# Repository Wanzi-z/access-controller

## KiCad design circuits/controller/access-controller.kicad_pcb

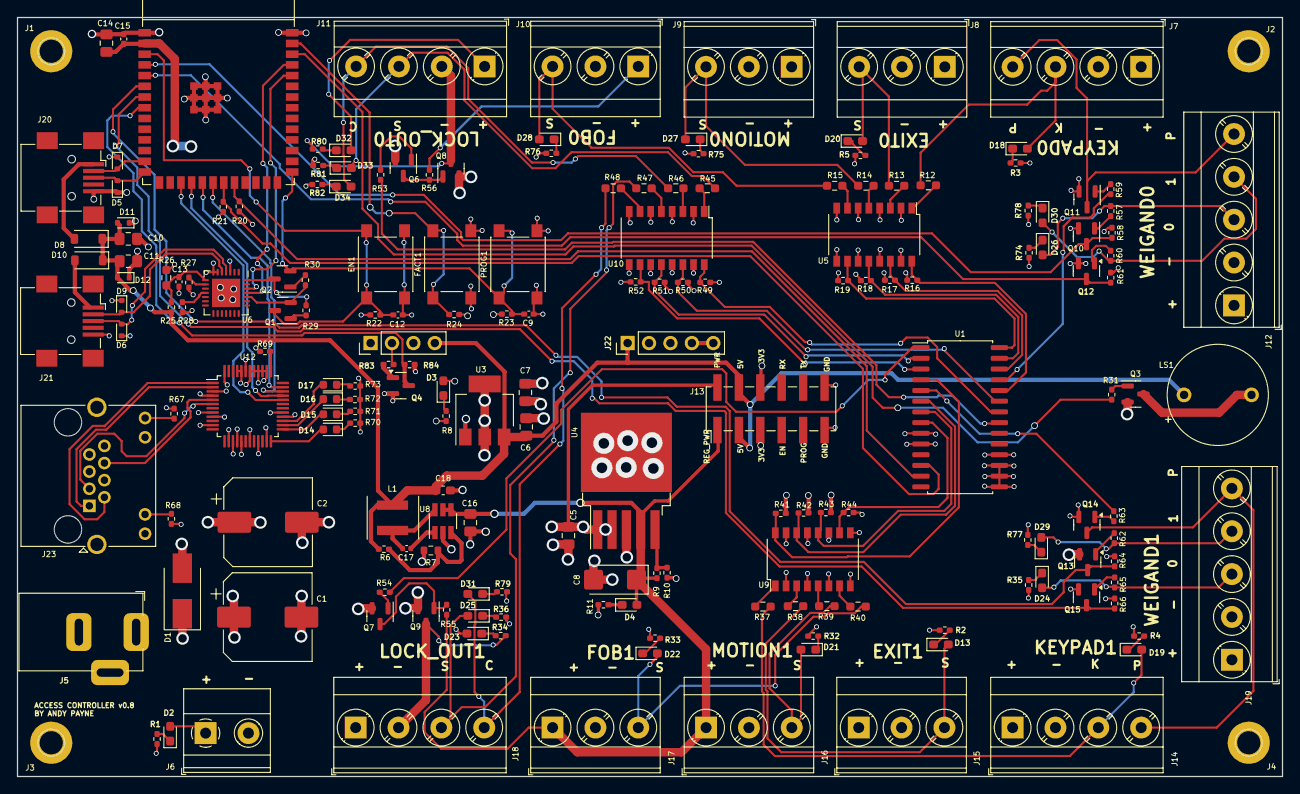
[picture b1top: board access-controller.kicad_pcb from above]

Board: 4 copper layers, 150.0 x 90.0 mm, 186 parts (0 on the bottom side), 138 nets.

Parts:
C1, C2: C_470uF; CP_Elec_10x10
C5, C6, C7, C10, C11, C14, C16: C_10uF; C_0805_2012Metric_Pad1.18x1.45mm_HandSolder
C8: C_10uF_Ta; CP_EIA-6032-15_Kemet-U_Pad2.25x2.35mm_HandSolder
C9, C12, C13: 1uF; C_0402_1005Metric_Pad0.74x0.62mm_HandSolder
C15: 100nF; C_0402_1005Metric_Pad0.74x0.62mm_HandSolder
C17: 22nF; C_0402_1005Metric
C18: C_22uF; C_0603_1608Metric_Pad1.08x0.95mm_HandSolder
D1: D_Zener; D_SMB_Handsoldering
D2, D3, D4, D13, D18, D19, D20, D21, D22, D23, D24, D25, D26, D27, D28, D29, D30, D31, D32, D33, D34: White; LED_0603_1608Metric_Pad1.05x0.95mm_HandSolder
D5, D6, D7, D9, D11, D12: ESD_5V; D_SOD-523
D8, D10: D_1N5819HW; D_SOD-123
D14, D15, D16, D17: Red; LED_0603_1608Metric
EN1: SW_PUSH; SW_SPST_PTS645
FACT1: SW_PUSH; SW_SPST_PTS645
J1, J2, J3, J4: Conn_01x01_Female; Mount_Hole
J5: Barrel_Jack_Switch; BarrelJack_OD5.5_ID2.5
J6: Screw_Terminal_01x02; TerminalBlock_Phoenix_MKDS-1,5-2-5.08_1x02_P5.08mm_Horizont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
J7, J11, J14, J18: Terminal_01x04; TerminalBlock_Phoenix_MKDS-3-4-5.08_1x04_P5.08mm_Horizontal
J8, J9, J10, J15, J16, J17: Terminal_01x03; TerminalBlock_Phoenix_MKDS-3-3-5.08_1x03_P5.08mm_Horizontal
J12, J19: Screw_Terminal_01x05; TerminalBlock_Phoenix_MKDS-3-5-5.08_1x05_P5.08mm_Horizontal
J13: Conn_02x06_Odd_Even; PinHeader_2x06_P2.54mm_Vertical_SMD
J20, J21: USB_MINI_B; USB_Mini-B_Wuerth_65100516121_Horizontal
J22: RF_MODULE; RXB6_RF_MODULE
J23: CONN_RJ45; RJ45_Amphenol_RJHSE538X
L1: 10uH; L_4x4
LS1: TMB12A05; S_YXDZ
PROG1: SW_PUSH; SW_SPST_PTS645
Q1: Q_L8050QLT1G; SOT-23
Q2: Q_L8550HQLT1G; SOT-23
Q3, Q4, Q6, Q7, Q10, Q11, Q12, Q13, Q14, Q15: Q_MMBT5551; SOT-23
Q8, Q9: Q_AO3400A; SOT-23
R1, R2, R3, R4, R5, R8, R11, R20, R21, R22, R23, R24, R28, R29, R30, R32, R33, R34, R35, R36, R67, R68, R74, R75, R76, R77, R78, R79, R80, R81, R82, R83, R84: 10K; R_0402_1005Metric_Pad0.72x0.64mm_HandSolder
R6: 100K; R_0402_1005Metric_Pad0.72x0.64mm_HandSolder
R7: 13K; R_0603_1608Metric
R9: R_20K; R_0402_1005Metric_Pad0.72x0.64mm_HandSolder
R10: R_2.2K; R_0402_1005Metric_Pad0.72x0.64mm_HandSolder
R12, R13, R14, R15, R37, R38, R39, R40, R45, R46, R47, R48: R_1K; R_0603_1608Metric_Pad0.98x0.95mm_HandSolder
R16, R17, R18, R19, R41, R42, R43, R44, R49, R50, R51, R52, R53, R54, R55, R56: R_10K_0402; R_0402_1005Metric_Pad0.72x0.64mm_HandSolder
R25: 22.1K; R_0402_1005Metric_Pad0.72x0.64mm_HandSolder
R26: 47.5K; R_0603_1608Metric_Pad0.98x0.95mm_HandSolder
R27, R69, R70, R71, R72, R73: 1K; R_0402_1005Metric_Pad0.72x0.64mm_HandSolder
R31, R59, R63: R_100; R_0402_1005Metric_Pad0.72x0.64mm_HandSolder
R57, R58, R60, R61, R62, R64, R65, R66: R_1K_0402; R_0402_1005Metric_Pad0.72x0.64mm_HandSolder
U1: MCP23017_SS; SOIC-28W_7.5x17.9mm_P1.27mm
U3: REG_AMS1117-3.3; SOT-223-3_TabPin2
U4: MIC29302WU; TO-263-5_TabPin3
U5, U9, U10: TLP291-4; SOP-16_4.4x10.4mm_P1.27mm
U6: CP2102N-Axx-xQFN28; QFN-28-1EP_5x5mm_P0.5mm_EP3.35x3.35mm
U7: ESP32-S3-WROOM-1
U8: REG_MT2492; SOT-23-6_Handsoldering
U12: W5500; LQFP-48_7x7mm_P0.5mm

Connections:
/3V3: C7.1, C14.1, C15.1, D3.2 (A), J13.5, J13.6, R16.1, R17.1, R18.1, R19.1, R20.1, R21.2, R22.1, R23.1, R24.1, R27.1, R41.1, R42.1, R43.1, R44.1, R49.1, R50.1, R51.1, R52.1, R58.2, R61.2, R64.2, R66.2, R67.2, R69.2, R84.1, U1.9 (VDD), U1.18 (~RESET), U3.2 (Vout), U6.6 (VDD), U6.7 (VREGIN), U7.2 (3V3), U12.4 (AVDD), U12.8 (AVDD), U12.11 (AVDD), U12.15 (AVDD), U12.17 (AVDD), U12.21 (AVDD), U12.28 (VDD), U12.43 (PMODE2)
/5V: C6.1, C10.1, C11.1, C18.1, D8.1 (K), D10.1 (K), D11.2 (A2), D12.2 (A2), J13.3, J13.4, J22.4, J22.5, L1.2, LS1.1, R6.1, R25.2, U3.3 (Vin)
/ANTENNA: J22.8, J22.9
/BUZZER: R31.1, U7.38 (GPIO2/TOUCH2/ADC1_CH1)
/CS: U7.17 (GPIO9/TOUCH9/ADC1_CH8/FSPIHD/SUBSPIHD), U12.32 (~SCS)
/DATA: J22.2, R83.2
/DATA_IO: Q4.3 (C), R84.2, U7.8 (GPIO15/U0RTS/ADC2_CH4/XTAL_32K_P)
/EXIT0: D20.2 (A), J8.3, R13.2
/EXIT0_SENSE: R17.2, U1.26 (GPA5), U5.14
/EXIT1: D13.2 (A), J15.3, R38.2
/EXIT1_SENSE: R42.2, U1.6 (GPB5), U9.14
/Ethernet/RX_N: J23.6, U12.5 (RXN)
/Ethernet/RX_P: J23.3, U12.6 (RXP)
/Ethernet/TX_N: J23.2, U12.1 (TXN)
/Ethernet/TX_P: J23.1, U12.2 (TXP)
/FOB0: D28.2 (A), J10.3, R15.2
/FOB0_SENSE: R19.2, U1.28 (GPA7), U5.10
/FOB1: D22.2 (A), J17.3, R40.2
/FOB1_SENSE: R44.2, U1.8 (GPB7), U9.10
/KEYPAD0: D18.2 (A), J7.3, R12.2
/KEYPAD0_SENSE: R16.2, U1.24 (GPA3), U5.16
/KEYPAD1: D19.2 (A), J14.3, R37.2
/KEYPAD1_SENSE: R41.2, U1.4 (GPB3), U9.16
/LOCK0_CLOSE: D34.2 (A), J11.4, R46.2
/LOCK0_CLOSE_IO: R50.2, U1.23 (GPA2), U10.14
/LOCK0_CONTROL: R53.2, U1.21 (GPA0)
/LOCK0_OUT: J11.2, Q8.3 (D), R80.1
/LOCK0_SENSE: R49.2, U1.22 (GPA1), U10.16
/LOCK0_STATE: D33.2 (A), J11.3, R45.2
/LOCK1_CLOSE: D31.2 (A), J18.4, R48.2
/LOCK1_CLOSE_IO: R52.2, U1.3 (GPB2), U10.10
/LOCK1_CONTROL: R54.2, U1.1 (GPB0)
/LOCK1_OUT: J18.2, Q9.3 (D), R34.1
/LOCK1_SENSE: R51.2, U1.2 (GPB1), U10.12
/LOCK1_STATE: D25.2 (A), J18.3, R47.2
/MISO: U7.20 (GPIO12/TOUCH12/ADC2_CH1/FSPICLK/FSPIIO6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), U12.34 (MISO)
/MOSI: U7.19 (GPIO11/TOUCH11/ADC2_CH0/FSPID/FSPIIO5/S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), U12.35 (MOSI)
/MOTION0: D27.2 (A), J9.3, R14.2
/MOTION0_SENSE: R18.2, U1.27 (GPA6), U5.12
/MOTION1: D21.2 (A), J16.3, R39.2
/MOTION1_SENSE: R43.2, U1.7 (GPB6), U9.12
/Microcontroller/D+: D6.2 (A2), J21.3 (D+), U6.4 (D+)
/Microcontroller/D-: D9.2 (A2), J21.2 (D-), U6.5 (D-)
/Microcontroller/DTR: Q2.3 (C), R29.1, U6.28 (~DTR)
/Microcontroller/EN: C12.1, EN1.1, Q1.3 (C), R22.2, U7.3 (EN)
/Microcontroller/FACT: FACT1.1, R24.2, U7.39 (GPIO1/TOUCH1/ADC1_CH0)
/Microcontroller/IO19: D7.2 (A2), J20.2 (D-), U7.13 (GPIO19/U1RTS/ADC2_CH8/CLK_OUT2/USB_D-)
/Microcontroller/IO20: D5.2 (A2), J20.3 (D+), U7.14 (GPIO20/U1CTS/ADC2_CH9/CLK_OUT1/USB_D+)
/Microcontroller/IO43: U6.25 (RXD), U7.37 (U0TXD/GPIO43/CLK_OUT1)
/Microcontroller/IO44: U6.26 (TXD), U7.36 (U0RXD/GPIO44/CLK_OUT2)
/Microcontroller/PROG: C9.1, PROG1.1, Q2.2 (E), R23.2, U7.27 (GPIO0/BOOT)
/Microcontroller/RTS: Q1.2 (E), R30.1, U6.24 (~RTS)
/POWER: C1.1, C2.1, C5.1, D1.1 (K), D2.2 (A), D23.2 (A), D32.2 (A), J5.1, J6.1, J11.1, J13.2, J18.1, J23.4, J23.5, R68.2, U4.1 (EN), U4.2 (IN)
/PUSH0: J7.4, J12.5, Q11.3 (C)
/PUSH0_IO: R59.1, U1.25 (GPA4)
/PUSH1: J14.4, J19.5, Q14.3 (C)
/PUSH1_IO: R63.1, U1.5 (GPB4)
/REG_POWER: C8.1, C16.1, D4.2 (A), J7.1, J8.1, J9.1, J10.1, J12.1, J13.1, J14.1, J15.1, J16.1, J17.1, J19.1, R9.1, R55.2, R56.2, U4.4 (Output), U8.4 (EN), U8.5 (VIN)
/SCL: R21.1, U1.12 (SCK), U7.21 (GPIO13/TOUCH13/ADC2_CH2/FSPIQ/FSPIIO7/S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)
/SCLK: U7.18 (GPIO10/TOUCH10/ADC1_CH9/FSPICS0/FSPIIO4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), U12.33 (SCLK)
/SDA: R20.2, U1.13 (SDA), U7.22 (GPIO14/TOUCH14/ADC2_CH3/FSPIWP/FSPIDQS/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)
/WG0_DATA0: D26.2 (A), J12.3, R57.2
/WG0_DATA1: D30.2 (A), J12.4, R60.2
/WG0_DATA_SENSE0: Q10.3 (C), R58.1, U7.4 (GPIO4/TOUCH4/ADC1_CH3)
/WG0_DATA_SENSE1: Q12.3 (C), R61.1, U7.5 (GPIO5/TOUCH5/ADC1_CH4)
/WG1_DATA0: D24.2 (A), J19.3, R65.2
/WG1_DATA1: D29.2 (A), J19.4, R62.2
/WG1_DATA_SENSE0: Q13.3 (C), R64.1, U7.6 (GPIO6/TOUCH6/ADC1_CH5)
/WG1_DATA_SENSE1: Q15.3 (C), R66.1, U7.7 (GPIO7/TOUCH7/ADC1_CH6)
GND: C1.2, C2.2, C5.2, C6.2, C7.2, C8.2, C9.2, C10.2, C11.2, C12.2, C13.2, C14.2, C15.2, C16.2, C18.2, D1.2 (A), D5.1 (A1), D6.1 (A1), D7.1 (A1), D9.1 (A1), D11.1 (A1), D12.1 (A1), EN1.2, FACT1.2, J1.1, J2.1, J3.1, J4.1, J5.2, J5.3, J6.2, J7.2, J8.2, J9.2, J10.2, J12.2, J13.11, J13.12, J14.2, J15.2, J16.2, J17.2, J19.2, J20.5 (GND), J21.5 (GND), J22.1, J22.6, J22.7, J23.7, J23.8, J23.9, J23.11, PROG1.2, Q3.2 (E), Q4.2 (E), Q6.2 (E), Q7.2 (E), Q8.2 (S), Q9.2 (S), Q10.2 (E), Q11.2 (E), Q12.2 (E), Q13.2 (E), Q14.2 (E), Q15.2 (E), R1.1, R2.1, R3.1, R4.1, R5.1, R7.2, R8.1, R10.2, R11.1, R26.1, R28.2, R32.1, R33.1, R35.1, R36.1, R70.2, R71.2, R72.2, R73.2, R74.1, R75.1, R76.1, R77.1, R78.1, R79.1, R81.1, R82.1, U1.10 (VSS), U1.15 (A0), U1.16 (A1), U1.17 (A2), U3.1 (GND), U4.3 (GND), U5.2, U5.4, U5.6, U5.8, U5.9, U5.11, U5.13, U5.15, U6.3 (GND), U6.29 (GND), U7.1 (GND), U7.40 (GND), U7.41 (GND), U8.2 (GND), U9.2, U9.4, U9.6, U9.8, U9.9, U9.11, U9.13, U9.15, U10.2, U10.4, U10.6, U10.8, U10.9, U10.11, U10.13, U10.15, U12.3 (AGND), U12.9 (AGND), U12.14 (AGND), U12.16 (AGND), U12.19 (AGND), U12.23 (RSVD), U12.29 (GND), U12.38 (RSVD), U12.39 (RSVD), U12.40 (RSVD), U12.41 (RSVD), U12.42 (RSVD), U12.44 (PMODE1), U12.45 (PMODE0), U12.48 (AGND)
unnamed: D2.1 (K), R1.2
unnamed: D3.1 (K), R8.2
unnamed: D4.1 (K), R11.2
unnamed: D8.2 (A), J20.1 (VBUS)
unnamed: D10.2 (A), J21.1 (VBUS)
unnamed: D13.1 (K), R2.2
unnamed: D14.2 (A), U12.24 (SPDLED)
unnamed: D14.1 (K), R70.1
unnamed: D15.2 (A), U12.25 (LINKLED)
unnamed: D15.1 (K), R71.1
unnamed: D16.2 (A), U12.26 (DUPLED)
unnamed: D16.1 (K), R72.1
unnamed: D17.2 (A), U12.27 (ACTLED)
unnamed: D17.1 (K), R73.1
unnamed: D18.1 (K), R3.2
unnamed: D19.1 (K), R4.2
unnamed: D20.1 (K), R5.2
unnamed: D21.1 (K), R32.2
unnamed: D22.1 (K), R33.2
unnamed: D23.1 (K), R34.2
unnamed: D24.1 (K), R35.2
unnamed: D25.1 (K), R36.2
unnamed: D26.1 (K), R74.2
unnamed: D27.1 (K), R75.2
unnamed: D28.1 (K), R76.2
unnamed: D29.1 (K), R77.2
unnamed: D30.1 (K), R78.2
unnamed: D31.1 (K), R79.2
unnamed: D32.1 (K), R80.2
unnamed: D33.1 (K), R81.2
unnamed: D34.1 (K), R82.2
unnamed: J23.10, R68.1
unnamed: J23.12, R67.1
unnamed: Q1.1 (B), R29.2
unnamed: Q2.1 (B), R30.2
unnamed: Q3.1 (B), R31.2
unnamed: LS1.2, Q3.3 (C)
unnamed: Q4.1 (B), R83.1
unnamed: Q6.1 (B), R53.1
unnamed: Q6.3 (C), Q8.1 (G), R56.1
unnamed: Q7.1 (B), R54.1
unnamed: Q7.3 (C), Q9.1 (G), R55.1
unnamed: Q10.1 (B), R57.1
unnamed: Q11.1 (B), R59.2
unnamed: Q12.1 (B), R60.1
unnamed: Q13.1 (B), R62.1
unnamed: Q14.1 (B), R63.2
unnamed: Q15.1 (B), R65.1
unnamed: R12.1, U5.1
unnamed: R13.1, U5.3
unnamed: R14.1, U5.5
unnamed: R15.1, U5.7
unnamed: R37.1, U9.1
unnamed: R38.1, U9.3
unnamed: R39.1, U9.5
unnamed: R40.1, U9.7
unnamed: R45.1, U10.1
unnamed: R46.1, U10.3
unnamed: R47.1, U10.5
unnamed: R48.1, U10.7
unnamed: R9.2, R10.1, U4.5 (Feedback)
unnamed: C13.1, R25.1, R26.2, U6.8 (VBUS)
unnamed: R27.2, U6.9 (~RST)
unnamed: R28.1, U6.11 (~SUSPEND)
unnamed: C17.1, U8.1 (BS)
unnamed: R6.2, R7.1, U8.3 (FB)
unnamed: C17.2, L1.1, U8.6 (SW)
unnamed: R69.1, U12.37 (~RST)

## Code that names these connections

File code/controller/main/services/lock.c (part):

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#define NUM_OF_LOCKS        2

/* Channel 1 = LOCK0: GPA1=SENSE, GPA2=CLOSE_IO. Channel 2 = LOCK1: GPB1=SENSE, GPB2=CLOSE_IO */
const uint8_t LOCK_CONTACT_PIN_1 = A2;  /* LOCK0_CLOSE_IO (GPA2) */
const uint8_t LOCK_CONTACT_PIN_2 = B2;  /* LOCK1_CLOSE_IO (GPB2) */

const uint8_t LOCK_SIGNAL_PIN_1 = A1;   /* LOCK0_SENSE (GPA1) */
const uint8_t LOCK_SIGNAL_PIN_2 = B1;   /* LOCK1_SENSE (GPB1) */

bool ARM = false;
bool ALERT = true;
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
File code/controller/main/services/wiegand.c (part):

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

void wiegand_main(void) {
	wg[0].pin0 = WG0_DATA0_IO;
	wg[0].pin1 = WG0_DATA1_IO;
	wg[0].pin_push = OPEN_IO_1;
	wg[0].delay = 4;
	wg[0].keypressTimeout = 10;  /* seconds before buffer clear; PIN only evaluated on # key */
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    wiegand_reset_bit_buffer(&wg[0]);
	strcpy(wg[0].name, "Wiegand0");

	wg[1].pin0 = WG1_DATA0_IO;
	wg[1].pin1 = WG1_DATA1_IO;
	wg[1].pin_push = OPEN_IO_1;
	wg[1].delay = 4;
	wg[1].keypressTimeout = 10;  /* seconds before buffer clear; PIN only evaluated on # key */
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
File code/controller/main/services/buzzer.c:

struct buzzer
{
	uint8_t pin;
	uint8_t beepCount;
	uint8_t longBeepCount;
	bool enable;
	bool quietTestMode;
	bool contactAlert;
};

struct buzzer bzr;

// MCP23017 pins for keypad push/beep signal.
// Hardware: MCP pin drives an NPN transistor base (via resistor). So:
// - MCP HIGH  => transistor ON  => keypad PUSH line pulled LOW (active at the connector)
// - MCP LOW   => transistor OFF => keypad PUSH line released (idle)
// From schematic: PUSH0_IO = GPA4 (index 4), PUSH1_IO = GPB4 (index 12)
#define MCP_PUSH0_IO  4   // Port A, pin 4
#define MCP_PUSH1_IO  12  // Port B, pin 4 (8 + 4 = 12)
#define KEYPAD_PUSH_ACTIVE_MS 750
#define KEYPAD_PUSH_IDLE_MS 100

// External MCP23017 functions
extern void set_mcp_io(uint8_t io, bool val);
extern void set_mcp_io_dir(uint8_t io, bool dir);

static const char *BUZZER_TAG = "buzzer";

static void keypad_push_set(uint8_t push_pin, bool active) {
    if (USE_MCP23017) {
        ESP_LOGI(BUZZER_TAG, "MCP PUSH pin %d -> %s", push_pin, active ? "HIGH (active)" : "LOW (idle)");
        set_mcp_io(push_pin, active);
    } else {
        gpio_set_level(OPEN_IO_1, active ? 1 : 0);
    }
}

static void alert_output_internal(int beeps, int channel, int target, bool force) {
    if (!bzr.enable) return;
    if (bzr.quietTestMode && !force) return;
    target = alert_target_normalize(target, true);
    if (target == ALERT_TARGET_NONE) return;

    bool push_wg1 = (target & ALERT_TARGET_WG1) != 0;
    bool push_wg2 = (target & ALERT_TARGET_WG2) != 0;

    ESP_LOGI(BUZZER_TAG, "alert_output: beeps=%d, channel=%d, target=%s, wg1=%d wg2=%d",
             beeps, channel, alert_target_to_string(target), push_wg1 ? 1 : 0, push_wg2 ? 1 : 0);

    for (int i = 0; i < beeps; i++) {
        if (target & ALERT_TARGET_CONTROLLER) {
            gpio_set_level(bzr.pin, 1);
        }
        
        if (push_wg1) {
            keypad_push_set(MCP_PUSH0_IO, true);
        }
        if (push_wg2) {
            keypad_push_set(MCP_PUSH1_IO, true);
        }
        
        vTaskDelay(pdMS_TO_TICKS(KEYPAD_PUSH_ACTIVE_MS));
        
        if (target & ALERT_TARGET_CONTROLLER) {
            gpio_set_level(bzr.pin, 0);
        }
        
        if (push_wg1) {
            keypad_push_set(MCP_PUSH0_IO, false);
        }
        if (push_wg2) {
            keypad_push_set(MCP_PUSH1_IO, false);
        }
        
        vTaskDelay(pdMS_TO_TICKS(KEYPAD_PUSH_IDLE_MS));
    }
}

void alert_output_signal(int beeps, int channel, int target) {
    alert_output_internal(beeps, channel, target, false);
}

void alert_output_signal_force(int beeps, int channel, int target) {
    alert_output_internal(beeps, channel, target, true);
}

void beep_keypad(int beeps, int channel) {
    alert_output_internal(beeps, channel, ALERT_TARGET_BOTH, false);
}

void beep_keypad_force(int beeps, int channel) {
    alert_output_internal(beeps, channel, ALERT_TARGET_BOTH, true);
}

void keypad_push_test(int channel, int pulses, int active_ms, int idle_ms, bool active_high) {
    if (pulses < 1) pulses = 1;
    if (pulses > 10) pulses = 10;
    if (active_ms < 20) active_ms = 20;
    if (active_ms > 3000) active_ms = 3000;
    if (idle_ms < 20) idle_ms = 20;
    if (idle_ms > 3000) idle_ms = 3000;

    uint8_t push_pin = (channel == 2) ? MCP_PUSH1_IO : MCP_PUSH0_IO;
    bool active_level = active_high;
    bool idle_level = !active_level;

    ESP_LOGI(BUZZER_TAG,
             "keypad_push_test: channel=%d MCP_PIN=%d pulses=%d active_ms=%d idle_ms=%d active_level=%d",
             channel, push_pin, pulses, active_ms, idle_ms, active_level ? 1 : 0);

    if (USE_MCP23017) {
        set_mcp_io_dir(push_pin, 0);
        set_mcp_io(push_pin, idle_level);
    } else {
        gpio_set_direction(OPEN_IO_1, GPIO_MODE_OUTPUT);
        gpio_set_level(OPEN_IO_1, idle_level);
    }
    vTaskDelay(pdMS_TO_TICKS(idle_ms));

    for (int i = 0; i < pulses; i++) {
        if (USE_MCP23017) {
            ESP_LOGI(BUZZER_TAG, "PUSH test pin %d -> %d", push_pin, active_level ? 1 : 0);
            set_mcp_io(push_pin, active_level);
        } else {
            gpio_set_level(OPEN_IO_1, active_level);
        }
        vTaskDelay(pdMS_TO_TICKS(active_ms));

        if (USE_MCP23017) {
            ESP_LOGI(BUZZER_TAG, "PUSH test pin %d -> %d", push_pin, idle_level ? 1 : 0);
            set_mcp_io(push_pin, idle_level);
        } else {
            gpio_set_level(OPEN_IO_1, idle_level);
        }
        if (i + 1 < pulses) {
            vTaskDelay(pdMS_TO_TICKS(idle_ms));
        }
    }
}

void buzzer_set_quiet_test_mode(bool enabled) {
    bzr.quietTestMode = enabled;
    ESP_LOGI(BUZZER_TAG, "Quiet test mode %s", enabled ? "enabled" : "disabled");
}

bool buzzer_get_quiet_test_mode(void) {
    return bzr.quietTestMode;
}

static void buzzer_task(void *pvParameter) {
  while (1) {
    // This task can be used for more complex patterns in the future
    vTaskDelay(SERVICE_LOOP / portTICK_PERIOD_MS);
  }
}

void buzzer_main() {
	bzr.pin = BUZZER_IO;
	bzr.enable = true;
	bzr.quietTestMode = false;
	bzr.contactAlert = true;
	bzr.longBeepCount = 0;
	bzr.beepCount = 0;

    gpio_set_direction(bzr.pin, GPIO_MODE_OUTPUT);
    gpio_set_level(bzr.pin, 0);

    // Ensure keypad PUSH output is OFF by default (idle).
    // (OPEN_IO_1 is configured as an output in gpio_main().)
    gpio_set_level(OPEN_IO_1, 0);

    // Initialize MCP PUSH pins as outputs (LOW = idle, HIGH = pulse)
    if (USE_MCP23017) {
        ESP_LOGI(BUZZER_TAG, "Initializing MCP PUSH pins: PUSH0=%d, PUSH1=%d as outputs", MCP_PUSH0_IO, MCP_PUSH1_IO);
        
        // PUSH0 for channel 1
        set_mcp_io_dir(MCP_PUSH0_IO, 0);  // 0 = output
        set_mcp_io(MCP_PUSH0_IO, 0);       // Default low (idle)
        
        // PUSH1 for channel 2
        set_mcp_io_dir(MCP_PUSH1_IO, 0);  // 0 = output
        set_mcp_io(MCP_PUSH1_IO, 0);       // Default low (idle)
        
        ESP_LOGI(BUZZER_TAG, "MCP PUSH pins initialized to LOW (idle)");
    }

    xTaskCreate(buzzer_task, "buzzer_task", 3072, NULL, 10, NULL);
}
